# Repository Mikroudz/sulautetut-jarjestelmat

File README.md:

<!-- PROJECT LOGO -->
<br />
<div align="center">

<h3 align="center">Balancing robot</h3>

  <p align="center">
    Two wheeled balancing robot using 6DoF accelerometer and gyroscope.
  </p>
</div>

<!-- TABLE OF CONTENTS -->
<details>
  <summary>Table of Contents</summary>
  <ol>
    <li>
      <a href="#about-the-project">About The Project</a>
      <ul>
        <li><a href="#built-with">Built With</a></li>
      </ul>
    </li>
    <li>
      <a href="#getting-started">Getting Started</a>
      <ul>
        <li><a href="#prerequisites">Prerequisites</a></li>
        <li><a href="#installation">Installation</a></li>
      </ul>
    </li>
    <li><a href="#usage">Usage</a></li>
    <li><a href="#roadmap">Roadmap</a></li>
    <li><a href="#contributing">Contributing</a></li>
    <li><a href="#license">License</a></li>
    <li><a href="#contact">Contact</a></li>
    <li><a href="#acknowledgments">Acknowledgments</a></li>
  </ol>
</details>

<!-- ABOUT THE PROJECT -->
## About The Project

[![Product Name Screen Shot][product-screenshot]](https://example.com)

<p align="right">(<a href="#top">back to top</a>)</p>

### Built With

* [Visual Studio Code](https://code.visualstudio.com/)
* [Platformio IO](https://platformio.org/)
* [STM32PIO](https://github.com/ussserrr/stm32pio)
* [CubeMX](https://www.st.com/en/development-tools/stm32cubemx.html)

<p align="right">(<a href="#top">back to top</a>)</p>

<!-- GETTING STARTED -->
## Getting Started

Easiest way to develop is with Visual Studio Code and Platformio. Template file generated with CubeMX and converted to VSCode format with STM32PIO. All tools work in both linux and windows operating systems. To program and debug the PCB, stlink interface is used and it requires a Nucleo development board or a Stlink programmer.

### Installation

1. Install Visual Studio Code for your distribution

2. Install Platformio IO inside Visual Studio Code.

3. Clone the project to your local PC
   ```sh
   git clone https://github.com/Mikroudz/sulautetut-jarjestelmat.git
   ```
4. Open project folder "STM32F410" in Visual Studio Code. Platformio should detect the project and install required compilation tools. Wait till it finishes.

## Programming the device
1. Connect a JTAG programming interface to the device and a Nucleo programmir header or JTAG programmer.

2. Power up the PCB with 11 - 16 volt power supply.

3. Insert USB to a pc with Visual Studio and platformio installed. The STM32 programmer should be detected.

4. Compile and program the device by pressing "Program" button in bottom of VSCode screen.

5. If successful the robots led should blink slowly.

<p align="right">(<a href="#top">back to top</a>)</p>

### Making configuration changes

To change I/O port configurations or device clocks, the project has been configured to use CubeMX tool. 
WARNING: if configurations are changed directly in the code, they will be overwritten by CubeMX.

1. Install CubeMX and open STM32F410.ioc file in the program.

2. Make changes and save the file.

3. Run [STM32PIO](https://github.com/ussserrr/stm32pio) on command line to update the project files:
   ```sh
   stm32pio generate -d path/to/ioc/file/folder
   ```

<!-- USAGE EXAMPLES -->
## Usage

After powering the robot and without LoRa connection it should be ready to balance. If the leds are blinking then hold the robot in upright position until it start to balance. If robot falls over too much forward or backwards, it stops the motors. 

<p align="right">(<a href="#top">back to top</a>)</p>

<!-- LICENSE -->
## License

Distributed under the MIT License. See `LICENSE.txt` for more information.

<p align="right">(<a href="#top">back to top</a>)</p>

<!-- ACKNOWLEDGMENTS -->
## Acknowledgments

* [@Mikroudz](https://github.com/Mikroudz)
* [@jruntti20](https://github.com/jruntti20)
* [@valtteriah](https://github.com/valtteriah)

<p align="right">(<a href="#top">back to top</a>)</p>

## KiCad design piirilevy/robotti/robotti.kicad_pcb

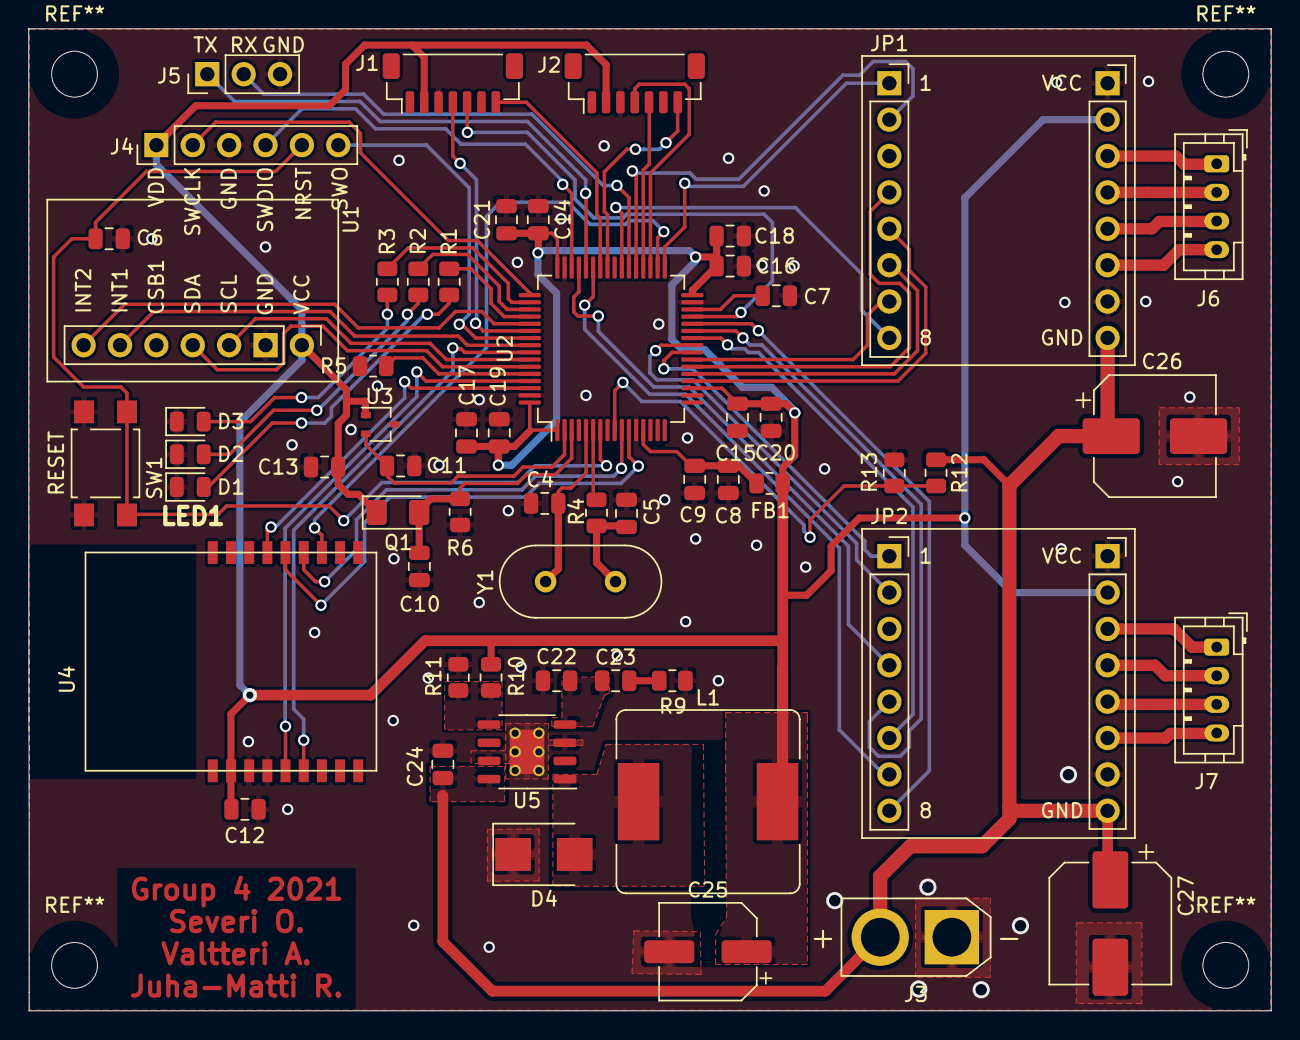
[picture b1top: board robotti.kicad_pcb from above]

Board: 2 copper layers, 86.8 x 68.6 mm, 58 parts (0 on the bottom side), 66 nets.

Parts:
C4, C5: 24pF; C_0805_2012Metric
C6, C13: 0.1uF; C_0805_2012Metric
C7: 4.7uF; C_0805_2012Metric
C8, C10, C18, C19, C20, C21: 1uF; C_0805_2012Metric
C9, C14, C15, C16, C17: 100nF; C_0805_2012Metric
C11: 680pF; C_0805_2012Metric
C12: 10uF; C_0805_2012Metric
C22: 39pF; C_0805_2012Metric
C23: 15nF; C_0805_2012Metric
C24: 2.2uF; C_0805_2012Metric
C25: 47uF; CP_Elec_6.3x5.4_Nichicon
C26, C27: 100uF; CP_Elec_8x5.4
D1, D2, D3: LED; LED_0805_2012Metric
D4: DIODE; D_SMB
FB1: Ferrite_Bead; R_0805_2012Metric
J1, J2: VL53L1X; JST_SH_BM07B-SRSS-TB_1x07-1MP_P1.00mm_Vertical
J3: XT30; AMASS_XT30U-F_1x02_P5.0mm_Vertical
J4: ST-LINK_V2; PinHeader_1x06_P2.54mm_Vertical
J5: UART; PinHeader_1x03_P2.54mm_Vertical
J6, J7: Nema14; JST_PH_B4B-PH-K_1x04_P2.00mm_Vertical
JP1, JP2: TMC2130-Connector_JP; TMC2130
L1: 15uH; L_Bourns_SRR1260
Q1: ALS-PT19-315C; D_1206_3216Metric_Pad1.42x1.75mm_HandSolder
R1, R2, R3: 150; R_0805_2012Metric
R4: 830; R_0805_2012Metric
R5: 10k; R_0805_2012Metric
R6: 10K; R_0805_2012Metric
R9, R11: 4.3K; R_0805_2012Metric
R10: 7.15K; R_0805_2012Metric
R12: 20K; R_0805_2012Metric
R13: 5K; R_0805_2012Metric
SW1: SW_SPST; SW_SPST_TL3305A
U1: SEN0373; PinHeader_1x07_PinHeader_SEN0373
U2: STM32F410RBTx; LQFP-64_10x10mm_P0.5mm
U3: TMP235; SOT-323_SC-70
U4: RC-SM1276-868
U5: L5973D; HSOP-8-1EP_3.9x4.9mm_P1.27mm_EP2.41x3.1mm_ThermalVias
Y1: ABL-8.000MHZ-B2; Crystal_HC49-U_Vertical

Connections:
/PA4: JP1.5, U2.20
/PA5: JP1.6, U2.21
/PA6: JP1.4, U2.22
/PA7: JP1.7, U2.23
/PA8: J2.7, U2.41
/PA9: J1.7, U2.42
/PA10: JP2.7, U2.43
/PA11: J5.1, U2.44
/PA12: JP2.4, U2.45
/PA13: J4.4, U2.46
/PA14: J4.2, U2.49
/PA15: R3.1, U2.50
/PB0: JP2.6, U2.26
/PB1: JP2.5, U2.27
/PB2: JP2.8, U2.28
/PB3: J4.6, U2.55
/PB4: U1.6, U2.56
/PB5: U2.57, U4.6
/PB6: U1.3, U2.58
/PB7: U1.4, U2.59
/PB8: U2.61, U4.5
/PB9: U2.62, U4.15
/PB10: J1.5, U2.29
/PB11: J1.4, U2.54
/PB12: JP1.1, U2.33
/PB13: U2.34, U4.12
/PB14: J2.4, U2.35
/PB15: J2.5, U2.36
/PC1: R12.2, R13.2, U2.9
/PC2: U2.10, U4.13
/PC3: U2.11, U4.14
/PC4: JP2.1, U2.24
/PC5: JP2.2, U2.25
/PC6: JP1.2, U2.37
/PC7: J5.2, U2.38
/PC8: JP1.8, U2.39
/PC12: U1.7, U2.53
/PC13: C11.1, U2.2, U3.2
/PC14: C10.1, Q1.2, R6.1, U2.3
/VDDA: C8.2, C9.2, FB1.1, U2.13
GND: C4.2, C5.2, C6.2, C7.1, C8.1, C9.1, C10.2, C11.2, C12.2, C13.1, C14.1, C15.1, C16.1, C17.1, C18.2, C19.2, C20.2, C21.2, C22.1, C24.1, C25.2, C26.2, C27.2, D1.1, D2.1, D3.1, D4.1, J1.3, J2.3, J3.1, J4.3, J5.3, JP1.10, JP1.16, JP2.10, JP2.16, R5.2, R6.2, R9.2, R11.2, R13.1, SW1.1, U1.2, U2.12, U2.18, U2.31, U2.47, U2.63, U3.3, U4.3, U4.4, U5.3, U5.7, U5.9
NRST: C6.1, J4.5, SW1.2, U2.7
unnamed: C4.1, U2.5, Y1.1
unnamed: C5.1, R4.2, Y1.2
unnamed: C7.2, U2.30
unnamed: C22.2, C23.2, U5.4
unnamed: C23.1, R9.1
unnamed: D1.2, R1.2
unnamed: D2.2, R2.2
unnamed: D3.2, R3.2
unnamed: D4.2, L1.1, U5.1
unnamed: J6.1, JP1.14
unnamed: J6.2, JP1.13
unnamed: J6.3, JP1.12
unnamed: J6.4, JP1.11
unnamed: J7.1, JP2.14
unnamed: J7.2, JP2.13
unnamed: J7.3, JP2.12
unnamed: J7.4, JP2.11
unnamed: R1.1, U2.52
unnamed: R2.1, U2.51
unnamed: R4.1, U2.6
unnamed: R5.1, U2.60
unnamed: R10.2, R11.1, U5.5
VCC: C24.2, C26.1, C27.1, J3.2, JP1.9, JP2.9, R12.1, U5.8
VDD: C12.1, C13.2, C14.2, C15.2, C16.2, C17.2, C18.1, C19.1, C20.1, C21.1, C25.1, FB1.2, J1.2, J2.2, J4.1, JP1.15, JP2.15, L1.2, Q1.1, R10.1, U1.1, U2.1, U2.19, U2.32, U2.48, U2.64, U3.1, U4.2

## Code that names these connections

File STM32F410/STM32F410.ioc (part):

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Mcu.Name=STM32F410R(8-B)Tx
Mcu.Package=LQFP64
Mcu.UserName=STM32F410RBTx
PA10.Mode=Full_Duplex_Master
PA10.Signal=SPI5_MOSI
PA11.Mode=Asynchronous
PA11.Signal=USART6_TX
PA12.Mode=Full_Duplex_Master
PA12.Signal=SPI5_MISO
PA13.Mode=Trace_Asynchronous_SW
PA13.Signal=SYS_JTMS-SWDIO
PA14.Mode=Trace_Asynchronous_SW
PA14.Signal=SYS_JTCK-SWCLK
PA15.GPIOParameters=PinState,GPIO_Label
PA15.GPIO_Label=LED3
PA15.PinState=GPIO_PIN_SET
PA15.Signal=GPIO_Output
PA4.GPIOParameters=GPIO_Label
PA4.GPIO_Label=tmc2130_1_nss
PA4.Signal=GPIO_Output
PA5.Mode=Full_Duplex_Master
PA5.Signal=SPI1_SCK
PA6.Mode=Full_Duplex_Master
PA6.Signal=SPI1_MISO
PA7.Mode=Full_Duplex_Master
PA7.Signal=SPI1_MOSI
PA8.GPIOParameters=GPIO_Speed
PA8.GPIO_Speed=GPIO_SPEED_FREQ_VERY_HIGH
PA8.Mode=Clock-out-1
PA8.Signal=RCC_MCO_1
PA9.Signal=GPIO_Input
PB0.Mode=Full_Duplex_Master
PB0.Signal=SPI5_SCK
PB1.GPIOParameters=GPIO_Label
PB1.GPIO_Label=tmc2130_2_nss
PB1.Signal=GPIO_Output
PB10.Mode=I2C
PB10.Signal=I2C2_SCL
PB11.Mode=I2C
PB11.Signal=I2C2_SDA
PB12.GPIOParameters=GPIO_Label
PB12.GPIO_Label=tmc2130_1_dir
PB12.Signal=GPIO_Output
PB13.Mode=Full_Duplex_Master
PB13.Signal=SPI2_SCK
PB14.Mode=I2C
PB14.Signal=FMPI2C1_SDA
PB15.Mode=I2C
PB15.Signal=FMPI2C1_SCL
PB2.GPIOParameters=PinState,GPIO_Label
PB2.GPIO_Label=tmc2130_2_enable
PB2.PinState=GPIO_PIN_SET
PB2.Signal=GPIO_Output
PB3.Mode=Trace_Asynchronous_SW
PB3.Signal=SYS_JTDO-SWO
PB4.GPIOParameters=GPIO_Label
PB4.GPIO_Label=lora_tx_enable
PB4.Signal=GPIO_Output
PB5.GPIOParameters=GPIO_Label
PB5.GPIO_Label=lora_int
PB5.Signal=GPXTI5
PB6.GPIOParameters=GPIO_PuPdOD,GPIO_Label
PB6.GPIO_Label=IMU_I2C_SCL
PB6.GPIO_PuPdOD=GPIO_NOPULL
PB6.Mode=I2C
PB6.Signal=I2C1_SCL
PB7.GPIOParameters=GPIO_PuPdOD,GPIO_Label
PB7.GPIO_Label=IMU_i2C_SDA
PB7.GPIO_PuPdOD=GPIO_NOPULL
PB7.Mode=I2C
PB7.Signal=I2C1_SDA
PB8.GPIOParameters=GPIO_Label
PB8.GPIO_Label=lora_nreset
PB8.Signal=GPIO_Output
PB9.GPIOParameters=PinState
PB9.PinState=GPIO_PIN_RESET
PB9.Signal=GPIO_Output
PC1.GPIOParameters=GPIO_Label
PC1.GPIO_Label=vcc_meas
PC1.Signal=SharedAnalog_PC1
PC10.Signal=GPIO_Output
PC11.Signal=GPIO_Output
PC12.GPIOParameters=GPIO_Label
PC12.GPIO_Label=lora_rx_enable
PC12.Signal=GPIO_Output
PC13-ANTI_TAMP.Signal=GPIO_Analog
PC14-OSC32_IN.Signal=GPIO_Analog
PC2.Mode=Full_Duplex_Master
PC2.Signal=SPI2_MISO
PC3.Mode=Full_Duplex_Master
PC3.Signal=SPI2_MOSI
PC4.GPIOParameters=GPIO_Label
PC4.GPIO_Label=tmc2130_2_dir
PC4.Signal=GPIO_Output
PC5.GPIOParameters=GPIO_Label
PC5.GPIO_Label=tmc2130_2_step
PC5.Signal=GPIO_Output
PC6.GPIOParameters=GPIO_Speed,GPIO_Label
PC6.GPIO_Label=tmc2130_1_step
PC6.GPIO_Speed=GPIO_SPEED_FREQ_HIGH
PC6.Signal=GPIO_Output
PC7.Mode=Asynchronous
PC7.Signal=USART6_RX
PC8.GPIOParameters=PinState,GPIO_Label
PC8.GPIO_Label=tmc2130_1_enable
PC8.PinState=GPIO_PIN_SET
PC8.Signal=GPIO_Output
PC9.GPIOParameters=GPIO_Speed
PC9.GPIO_Speed=GPIO_SPEED_FREQ_VERY_HIGH
PC9.Mode=Clock-out-2
PC9.Signal=RCC_MCO_2
PH0\ -\ OSC_IN.Mode=HSE-External-Oscillator
PH0\ -\ OSC_IN.Signal=RCC_OSC_IN
PH1\ -\ OSC_OUT.Mode=HSE-External-Oscillator
PH1\ -\ OSC_OUT.Signal=RCC_OSC_OUT
RCC.HSE_VALUE=8000000
RCC.SYSCLKFreq_VALUE=96000000
RCC.SYSCLKSource=RCC_SYSCLKSOURCE_PLLCLK
board=custom

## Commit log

2021-03-25 init
2021-03-25 Aloitettu piirilevysuunnittelu
2021-03-25 MCU lisätty, jännitesyöttö ja kide
2021-03-25 Lisätty LoRa, etäisyys, lämpö- ja valoisuusanturi
2021-04-01 korjattu lämpömittari
2021-04-01 lisätty toinen etäisyyssensori + annotointi symboleille
2021-04-01 Regulointi lisätty
2021-04-08 Schema valmis + aloitettu pcb
2021-04-22 PCB V2.0
2021-04-22 Generoitu Platformio IO projekti CubeMX conffista
2021-04-28 vscode stuff
2021-04-28 Lisätty I/O porttien toiminnallisuus
2021-04-29 PCB korjattu ei valmis
2021-05-12 PCB final tilattu ver.
2021-05-12 i2c testi etäisyyssensorilla ja nucleo f303:lla
2021-05-26 UART toimii
2021-05-27 fix schema
2021-05-27 (Final) korjattu pcb
2021-06-04 LoRa testikoodi stm32f410 projektissa
2021-06-04 TMC2130 ajuri aloitettu (tmc2130.c ja .h)
2021-06-08 tmc2130 mod
2021-06-18 IMU testaus aloitettu
2021-07-01 started testing ihold irun register commands
2021-08-11 tmc2130 rekisterien lukeminen aloitettu
2021-08-11 loraa jatkettu
2021-08-11 Korjattu TMC2130 lukufunkkaria
2021-08-12 korjaus spi read functioon
2021-08-12 jotain
2021-08-12 debuggaustietoja lisätty rekisterinlukufunktioon
2021-08-12 Lisätty chopconf write read + bugi korjattu spi write-funktiosta
2021-08-12 Lisätty stepperiajofunktio
2021-09-05 Korjattu spi-luenta stepperiltä
2021-09-08 Korjattu tmc2130 ohjausta, lisätty IMU ja lora DMA luku
2021-09-08 Lorakorjauksia
2021-09-13 tmc2130 korjauksia
2021-09-14 Toimiva koodi stepper 1 ja 2
2021-09-16 Lisätty jänniteluenta akusta
2021-09-16 Korjattu puuttuvat interruptikäsittelijät
2021-10-11 2 stepperin tuki lisatty
2021-10-22 edgelaite
2021-11-02 fixed venv
2021-11-10 Restructured main loop to work with balance calc
2022-01-10 Working on new wheel position system
2022-01-12 Stepper angle control
2022-01-14 Testaamaton tasapainottelu
2022-01-28 Toimiva tasapainotus + paikkaohjaus
2022-02-02 Siistitty koodia
2022-02-02 Lisätty radio-ohjaus
2022-02-03 Korjaus ohjausjarjestelmaan, jannitteenmittauksen keskiarvoistus lisatty
2022-02-08 Siirretty stepperohjaimen luonti stepper-kirjaston sisaan
2022-02-08 Updated app.py
2022-02-14 Receive message
2022-02-14 Lisatty LoRa viestien parseeminen
2022-02-24 Korjattu tasapainottelun aloitus
2022-03-23 extensions.json
2022-03-23 sending works
2022-03-28 Receive & send working
2022-03-28 LoRa kommunikaatio toimiva
2022-04-05 Pieniä korjauksia
2022-04-05 Receive messages
2022-05-10 tof testaus aloitettu
2022-05-12 lukee etäisyystiedot tof -sensorilta ja tallentaa lukeman robot_data.distance_front muuttujaan. Tasapainoilu toimii myös ilman DMA-ta, DMA-implementaatio vielä kesken.
2022-06-11 Poistettu f303 testikansio
2022-06-11 Poistettu turha datasheet
2022-06-11 Lisätty readme
2022-06-11 Siivottu readme
2023-03-19 some minor modifications on tmc2130.c
2023-03-19 merged with juhis_experimental
2023-03-19 removed unnecessary definitions
2023-03-19 .vscode updated
2023-03-19 reinstalled platformio and got dev environment working again, made some small adjustments to timings
